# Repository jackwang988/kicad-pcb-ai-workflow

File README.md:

# KiCad PCB AI 工作流 · R10.0.2 稳定维护版

> **2026-11-21**：Windows / KiCad 10.0.8 的 60 mm 单面 8×8 LED 案例已完成原理图、PCB、原生 ERC/DRC 与 Gerber/BOM 工程导出，最终 **0 错误、0 警告、0 未连接**。135 条丝印压焊盘、64 条重叠、80 条字段差异的修复已沉淀为可复用指南。
>
> **稳定范围**：软件回归与公开单板 native 验证，不是全部 16 节点/板型/平台或硬件性能认证。实例字段编辑依赖单独构建、登记和验证的开源 MCP companion；**官方 Konnect 0.14.1 不能直接执行该编辑**。正式 freeze/工程签字、板厂 CAM/EQ、CPL、实物通电/热测试仍独立或未覆盖。

[最新 Release/校验和](https://github.com/jackwang988/kicad-pcb-ai-workflow/releases/latest) · [R10.0.2 说明](R10_0_2_RELEASE_NOTES.md) · [完整实测经验](docs/r10/07-led-e2e-and-silkscreen.md) · [源板与证据](development/fixtures/led-8x8-12v) · [开源 MCP companion](development/konnect-field-extension)

最小 Skill ZIP 只含通用技能；样板、测试与 AGPL 补丁源码在独立 validation ZIP/仓库中。不携带编译器、商业后端或个人配置。正式产物以通过 CI 后生成的 ZIP/SHA/提交 provenance 为准。

## 早期 R10 验收记录（保留历史）

> **R10.0.0 软件稳定版发布目标（2026-11-18）**：基于已合并的 [PR #6](https://github.com/jackwang988/kicad-pcb-ai-workflow/pull/6)、[PR #7](https://github.com/jackwang988/kicad-pcb-ai-workflow/pull/7) 及 [GND 保护修复 PR #9](https://github.com/jackwang988/kicad-pcb-ai-workflow/pull/9)。原生 KiCad→Freerouting→SES→KiCad 保护测试已通过；正式 ZIP/标签须由 [稳定版 CI](.github/workflows/release-r10-stable.yml) 在 main 重新通过软件与原生测试后创建。**软件稳定≠任意PCB自动通过 G4 或授权投产。**
>
> **已验证范围**：KiCad 10.0.8 / Freerouting 2.5.0 隔离样板中，8条普通网络走线回导成功、GND新增走线为0（[原生测试](https://github.com/jackwang988/kicad-pcb-ai-workflow/actions/runs/44295612537)）；该样板仍有原生DRC 9项违规与2项未连接，**不能称为G4通过**。更复杂的多层/高速/电源产品必须独立验收。

> **R10 维护者正式验收补充（2026-11-18）**：维护者确认 GND 优先铺铜规则的 Skill 验证通过，[PR #10](https://github.com/jackwang988/kicad-pcb-ai-workflow/pull/10) 已合并至 `main`（提交 [`86b363f4408a`](https://github.com/jackwang988/kicad-pcb-ai-workflow/commit/86b363f4408af9b5cbd9a9eb7a972f9f65739555)）。现行流程强制**先第一次GND填铜→地铜连通与孤岛检查→按需添加批准的缝合地孔→再次填铜保存→全板DRC→G4**。维护者验收单独登记；[PR #12](https://github.com/jackwang988/kicad-pcb-ai-workflow/pull/12) 又修复了 KiCad 10 名称式网络及板文件格式规范化，[原生铺铜集成 CI #44331681459](https://github.com/jackwang988/kicad-pcb-ai-workflow/actions/runs/44331681459) **已通过**（首铺 F.Cu/B.Cu → 审核地孔 → 再次铺铜 → 原生 DRC）；但该合成样板 DRC 仍有 **13 项违规、3 项未连接**，因此 **并非 G4/制造放行**。详见 [R10 验收矩阵](docs/r10/05-release-readiness.md)。已有的 `R10.0.0` 标签是本次 PR #10 之前的历史快照，不能据此认定旧版ZIP包括新流程。

[核对 R10 正式版 Release 与 ZIP/SHA](https://github.com/jackwang988/kicad-pcb-ai-workflow/releases) · [R10.0.0 说明](R10_STABLE_RELEASE_NOTES.md) · [当前源码](https://github.com/jackwang988/kicad-pcb-ai-workflow/tree/main/kicad-pcb-ai-workflow) · [16节点及七阶段完整流程图](docs/r10/06-current-skill-full-flow.md) · [布线工程契约](kicad-pcb-ai-workflow/references/freerouting-seven-stage.md) · [验收矩阵](docs/r10/05-release-readiness.md) · [R9.4历史包](dist/kicad-pcb-ai-workflow-R9.4.zip)

## 一、R10 核心架构

```mermaid
flowchart TD
  U["用户需求 / 已有 KiCad 项目"] --> W["唯一工作工程 CURRENT_PROJECT.json"]
  W --> S["原厂资料缓存 / 芯片知识卡 / 精确网络拓扑"]
  S --> R["系统架构与原理图预布局 → G1 ERC → G2 封装"]
  R --> D["真实叠层 / NetClass / 制造规则生效与回读"]
  D --> P["Konnect 布局 / 保存与位置回读 → G3"]
  P --> C["关键网络由已验收 KiCad/Konnect 优先布线"]
  C --> F["Freerouting 2.5.0 普通网络 DSN → SES 候选"]
  F --> I["独立 KiCad 候选回导、保存重载、差异审核"]
  I --> O["有界修复 / GND 铺铜 / 原生完整 DRC"]
  O --> G["G4 逐层 PCB 审核 / 工程师确认"]
  G --> N["DFX/NPI → 冻结制造候选 Gerber/BOM/CPL"]
  N --> X["外部 CAM/EQ/工厂授权与试产（非 AI 自动放行）"]
  G -->|风险或证据未关闭| D
```

- **决策层**：AI结合需求、原厂资料、真实网络拓扑和工程规则生成受约束的操作计划；不能编造 datasheet、阻抗、层叠或通过结果。
- **执行层**：Konnect MCP是活动EDA工程的唯一受控写入者；动态发现实际能力，每次授权、写入、保存、回读和异常复核。Python负责只读解析、计算、规则/几何审计与证据绑定；KiCad原生CLI负责独立 ERC/DRC 与制造导出核验。
- **证据层**：器件卡片按制造商＋精确MPN＋封装缓存并复用于 G1/G2/G3/G4；单一权威 `01_WORKING` 工程、只读历史、不可覆盖里程碑、摘要阅读与完整本地审计证据同时保留。
- **门禁层**：任何未知网络、未生效规则、缺失工具、超出权限的改动、过期哈希或未关闭阻断问题均 `BLOCKED`；不能通过降低规则或删除对象制造通过状态。

## 二、16 节点工程全流程

| 节点 | 操作与真实产物 | 门禁 |
|---|---|---|
| 01–04 | 环境/工作区保护 → 量化需求与架构 → 原厂器件知识卡 → 0Ω/DNP/备用方案决策 | 输入来源与工程身份可追溯 |
| 05–07 | **先网络拓扑、预留布线通道及引脚空间，再摆放原理图器件** → 保存原生网络表/ERC → 符号封装脚号比对 | **G1 原理图，G2 封装** |
| 08 | 与板厂确认层叠、铜厚、线宽/线距、过孔、板边、差分/电源约束；在KiCad真实设置并回读 | 规则未生效不能布局/布线 |
| 09 | 连接器/安装孔锚定、模块布局、去耦与关键回路优化，Konnect保存及坐标回读 | **G3 仅布局专项审核**，允许飞线，**不做未布线全板DRC** |
| 10 | **关键网络优先 → Freerouting 普通网络 → SES回导 → 有界修复 → GND铺铜 → 原生DRC** | 七阶段布线契约及实际保存板审计 |
| 11 | 布线、过孔、参考地、回流路径、全部铜层、真实原生 DRC 和工程师确认 | **G4 最终PCB评审** |
| 12–13 | DFX/NPI → 独立冻结制造候选 → Gerber/Excellon/BOM/CPL/图纸及哈希 | `EXPORTED_NOT_RELEASED` |
| 14–16 | 工厂CAM/EQ与放行 → EVT/DVT/PVT → ECO归档 | **外部人工/实体流程**，不是AI自动执行或自动批准 |

详细输入/输出/失败回退：[最新全流程说明](kicad-pcb-ai-workflow/references/latest-complete-workflow.md)；[完整架构与实际运行流程图](docs/r10/06-current-skill-full-flow.md)。

## 三、PCB 七阶段布线执行标准（R10）

1. **完整网络清单**：依据保存的 KiCad PCB 和原生 XML Netlist 确定全部网络、`(Ref, Pin)` 端点、P0–P4 分类、电流、关键性、GND/NC，并检查真实 NetClass 归属。
2. **制造与设计规则先行**：取得板厂批准的层叠、铜厚、最小线宽/线距/过孔/板边，配置真实 NetClass、层限制、电源宽度、差分/等长及禁布区并重新读取验证。电源主干以实际电流/温升/压降计算和既定基准线宽为依据，额外保留**至少 0.254 mm 线宽余量**（不是统一固定宽度）；细脚仅允许经批准、有长度/区域上限的局部颈缩。
3. **关键网络优先并保护**：P0–P2等高优先级（高速/RF/差分/电源/Kelvin/时钟/开关回路）由已验收的 KiCad/Konnect 专项方式布线；保存、回读实际铜对象，保护原走线与锁定对象。
4. **Freerouting 2.5.0 批量普通网络**：保存 PCB 后导出 DSN，绑定 DSN/JAR 及获批准的 `.rules` SHA-256，使用 `-inc` 按**NetClass**排除 GND 与所有受保护网络类别；仅路由允许的普通 P3 网络，限制重试/时间/过孔，产生独立 `.ses` 候选。`-inc` 不是按网络名称排除；NetClass 必须确实覆盖全部网络。
5. **SES 导入与真实几何审核**：仅在隔离 KiCad 候选中经认可工具回导，保存/重载，对比网络、封装位置、原有关键铜与对象UUID，审核普通网络线宽、层、过孔、H/V/45°走线及完整性。**生成 SES 不等于成功布线。**
6. **有界修复**：仅处理明确的未连接项或获准的拆线白名单；执行前确认范围/限额，改动后重复真实回读；失败或工具缺失则阻断并交由工程师处理，不默认放宽工艺/电气规则。
7. **GND 首次铺铜 → 检查地铜连通 → 按需补地孔 → 再次铺铜 → 全板 DRC/G4**：GND不参与普通走线。先在批准的GND铜层真实覆铜并保存，审核孤岛、焊盘、回流路径和跨层铜区；仅在必要、合法且经批准的位置放置GND缝合过孔（并非见空白就打孔），**之后重新填铜、保存重载**。四份PCB快照通过只读 `pcb.ground_plane_audit`，才能执行 `kicad-cli pcb drc --refill-zones --save-board` 全板DRC与未连接检查。DRC不为零继续修复并再次覆铜；G4工程师签核独立。**铺铜前GND飞线不是最终DRC故障。**

[GND 铺铜、跨层地孔与 DRC 前置门禁规范](kicad-pcb-ai-workflow/references/gnd-before-drc.md)。GND 有多层填充不自动证明各层互连，最终须检查实际接触和原生网络连通性。

**注意**：Freerouting 2.5.0 不保证自动满足任意 KiCad 自定义 DRC、受控阻抗/等长/回流/局部颈缩，也不能仅凭 DSN/SES 证明最终角度45°；由导入后的实际铜和原生检查判定。审核脚本**只读**，不会自行执行 SES 导入、GND铺铜或原生DRC。

[七阶段详细参数与命令](kicad-pcb-ai-workflow/references/freerouting-seven-stage.md) · [主次布线与 NetClass 技术边界](kicad-pcb-ai-workflow/references/freerouting-primary-routing.md) · [设计约束](kicad-pcb-ai-workflow/references/constraint-routing.md)

## 四、部署与示例命令

**实际 Skill 位于仓库内的 [`kicad-pcb-ai-workflow/` 子目录](kicad-pcb-ai-workflow/)**，只安装这一层（包含 `SKILL.md`、`scripts/`、`references/`、`assets/`）。仓库根目录不是Skill安装目录。

- **使用R10当前源码**：`git clone https://github.com/jackwang988/kicad-pcb-ai-workflow.git`，再将仓库内部的 `kicad-pcb-ai-workflow/` 目录安装到 Agent Skills 目录。更新时以新目录完整替换、核对文件和原工程备份，勿与旧脚本混装。
- **已有正式包**：[R9.4稳定包](dist/kicad-pcb-ai-workflow-R9.4.zip)和 [R10.0.0-rc.1历史预发布包](dist/kicad-pcb-ai-workflow-R10.0.0-rc.1.zip)不包含本次全部合并改动；**不要当作最新版七阶段布线包**。
- **环境依赖**：匹配版本的 KiCad CLI/原生工程、可用的 Konnect MCP，普通网络自动布线还需要经SHA验证的 Freerouting **2.5.0 JAR** 和 Java，以及明确批准的厂规。Konnect/Freerouting为独立外部工具，不随Skill自动安装。`jsonschema>=4.18,<5` 见 [requirements.txt](requirements.txt)。
- **版本**：KiCad 10.0.7为历史推荐基线；KiCad 10.0.8曾完成独立原生工具链烟测。其它10.x必须实际验证能力；KiCad 9尚未开放未经验证的原生生产能力；KiCad 11+的CLI-only候选不等于PCB写入适配。

在Skill目录中以本机正确Python解释器运行，先预览、核对目标工程，再按需 `--apply`：

```bash
python scripts/workflow.py run /path/project --task environment.doctor
python scripts/workflow.py workspace /path/project --action status
python scripts/workflow.py status /path/project --bundle control-r1 --format compact
python scripts/workflow.py modules --intent pcb
python scripts/routing_seven_stage.py plan /path/project --config route-plan-config.json
# 仅在取得真实DSN/NetClass及厂规审核后运行候选
python scripts/freerouting_adapter.py --dsn route/board.dsn \
  --expected-dsn-sha256 ACTUAL_DSN_SHA \
  --netclass-map route/netclass-map.json \
  --expected-netclass-map-sha256 APPROVED_NATIVE_MAP_SHA \
  --jar approved/freerouting-2.5.0.jar \
  --expected-jar-sha256 APPROVED_JAR_SHA \
  --exclude-netclasses GND,DIFF_CRITICAL,RF_CRITICAL,POWER_CRITICAL \
  --output-dir NEW_CANDIDATE --passes 20
# 真实SES须在独立KiCad/Konnect工程中导入、保存、重载，再审计：
python scripts/routing_seven_stage.py audit-import /path/project --config route-import-config.json
# Konnect 在保存的 PCB 上先实际铺GND → 如需则添加已批准地孔 → 再次铺铜和保存重载。
python scripts/routing_seven_stage.py audit-ground /path/project --config ground-config.json --output reports/ground-pre-drc.json
# 只有审核通过，才能对完成铺铜的候选板运行全板 DRC：
kicad-cli pcb drc --refill-zones --save-board --format json --output reports/final-drc.json /path/project/checkpoints/final-refilled.kicad_pcb
# 再次保存回读，最后用 ground gate、post-DRC board 与 DRC report 的 SHA 审核：
python scripts/routing_seven_stage.py audit-final /path/project --config route-final-config.json
```

以上 Freerouting 命令默认仅生成预览，参数值和类名是示例，实际批准后再执行 `--apply`；如有 `.rules` 还必须显式给出其路径和SHA。参考 [环境配置](kicad-pcb-ai-workflow/references/environment-onboarding.md)、[工作区保护](kicad-pcb-ai-workflow/references/workspace-and-token-policy.md) 与 [模块化执行说明](kicad-pcb-ai-workflow/references/module-pcb.md)。

## 五、软件验收、原生验收与制造边界

| 层级 | 截至 2026-11-18 的状态 |
|---|---|
| PR #6 软件 CI | [已通过](https://github.com/jackwang988/kicad-pcb-ai-workflow/actions/runs/44278478257) |
| PR #7 软件 CI | [已通过](https://github.com/jackwang988/kicad-pcb-ai-workflow/actions/runs/44287952061) |
| KiCad 10.0.8 基础原生工具链 | [历史隔离工程烟测通过](https://github.com/jackwang988/kicad-pcb-ai-workflow/actions/runs/44015065144)，不等于新路由全链通过 |
| Windows/Konnect 本机 | **维护者报告已验收通过**；当前仓库没有相应的新现场日志/录屏可供独立复核 |
| KiCad→Freerouting 2.5.0→SES→KiCad 原生往返 | **PASS_NOT_G4**：[#44295612537](https://github.com/jackwang988/kicad-pcb-ai-workflow/actions/runs/44295612537)。GND在真实DSN中归属GND类；禁用v2.5.0 Fanout/Optimizer后，KiCad回导保存得到8条普通网线、0条新增GND铜线；旧版路由夹具在未铺地铜时出现过9项违规与2项未连；**不属于G4判定**。路由互通夹具已停止铺铜前全板DRC |
| PR #10 维护者 Skill 验收和源码合并 | **维护者已确认 PASS；[PR #10](https://github.com/jackwang988/kicad-pcb-ai-workflow/pull/10) 已合入 main**，含首次GND填充→批准地孔→再次填充→最终DRC门禁 |
| PR #10 软件 CI | [通过 #44321219956](https://github.com/jackwang988/kicad-pcb-ai-workflow/actions/runs/44321219956) |
| PR #12 原生铺铜修复及验收 | [**PASS_NOT_G4 · #44331681459**](https://github.com/jackwang988/kicad-pcb-ai-workflow/actions/runs/44331681459)：KiCad 10 双层 GND 首次铺铜、受审 GND 地孔、再次铺铜、保存回读、独立 DRC 实际执行；合成板仍有13项 DRC 违规/3项未连（非量产放行） |
| 不同层数/高速与电源混合项目、CAM/试产 | 未作为自动化通用能力认证；每个真实产品需独立验收 |

**修复记录（[PR #9](https://github.com/jackwang988/kicad-pcb-ai-workflow/pull/9) / [Issue #8](https://github.com/jackwang988/kicad-pcb-ai-workflow/issues/8)）**：仅有 NetClass 名称声明不够；必须校验网络实际 DSN 类成员与独立原生 `net_to_class` 全量映射及SHA-256。Freerouting 2.5.0 的 Fanout/Optimizer 在先前测试中绕开了GND保护，因此 R10普通网批量布线默认关闭这两阶段；回导后的受保护铜线差异审核继续强制执行。支持范围外保持 BLOCKED。

**软件发布不等于 PCB 可投产授权。** 源码测试、保存板上的G4 DRC、工程师的电气/热/高速审核以及板厂CAM/EQ/样机测试是独立步骤。Gerber、钻孔、BOM、CPL 导出成功仍标记 `EXPORTED_NOT_RELEASED`。

## 六、更多说明

[R10当前系统全流程与架构图](docs/r10/06-current-skill-full-flow.md) · [R10文档导航](docs/r10/README.md) · [原厂推荐电路与器件卡](kicad-pcb-ai-workflow/references/device-knowledge.md) · [原理图预布局门禁](kicad-pcb-ai-workflow/references/schematic-preplacement.md) · [G3布局规则](kicad-pcb-ai-workflow/references/placement-quality.md) · [DFX/NPI](kicad-pcb-ai-workflow/references/dfx-npi.md) · [能力与限制](kicad-pcb-ai-workflow/references/capabilities.md) · [MIT](LICENSE)

作者：[Jack](https://github.com/jackwang988) · 许可证：MIT。

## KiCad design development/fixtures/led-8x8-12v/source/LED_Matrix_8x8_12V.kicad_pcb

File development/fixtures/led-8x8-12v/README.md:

# Saved single-copper LED regression case

Source board SHA-256: `ff3a1ec530da8b8f27dfba17465142b448248b9a575763b118718e2d97a0c7ea`.
The nine source files are byte-identical to the final MCP-saved engineering export snapshot. Per-user `.kicad_prl`, logs, IPC configuration, executable files and absolute workstation paths are excluded. Exact source hashes and the local observation's **unverified** areas are in `evidence/observed-validation.json`.

60×60 mm, 8×8 red 2835 LEDs, 7.5 mm pitch, sixteen 4-LED + 1 kohm branches, 12 V DC, F.Cu only, no holes/vias. LED: Wurth Elektronik 150283RS73103, pin 1 anode / pin 2 cathode. Resistor: 1 kohm, 1%, 1206, 0.25 W; supplier/MPN unspecified. J1–J4 are PCB solder-pad pairs. Design material/thickness/copper are assumptions, not factory acceptance. See `design-basis.md`; this is a low-current workflow test, not an electrically measured product.

```sh
python -m pip install -r development/requirements-led-validation.txt
python development/native_led_8x8_e2e.py --kicad-cli /path/to/kicad-cli --output /new/native-led-check
```

Requires exact KiCad 10.0.8 plus its standard resistor footprint library, `power` symbol library and project custom libraries. On a new installation initialize **both** standard `fp-lib-table` and `sym-lib-table` through the normal installer/configuration. Installing library packages alone does not register them: the first clean Linux CI run correctly stopped on 44 missing-`power` ERC warnings. CI now initializes both tables in its disposable runner; the verifier never edits host library configuration or suppresses these warnings. The script exports/checks a new copy, compares all pads/tracks and net partitions, and requires zero native ERC/DRC warnings. It does not write the input, replay design creation, install/register MCP or satisfy the formal freeze/candidate gate.

`evidence/native-DRC.json` / `native-ERC.json` retain the observed zero-warning results. The metadata observation is a maintainer's local record; it is not an independent second-machine test. CI regenerates native reports rather than trusting those JSON counts. The final Gerber PNG is published under `docs/r10/figures` for the case account.

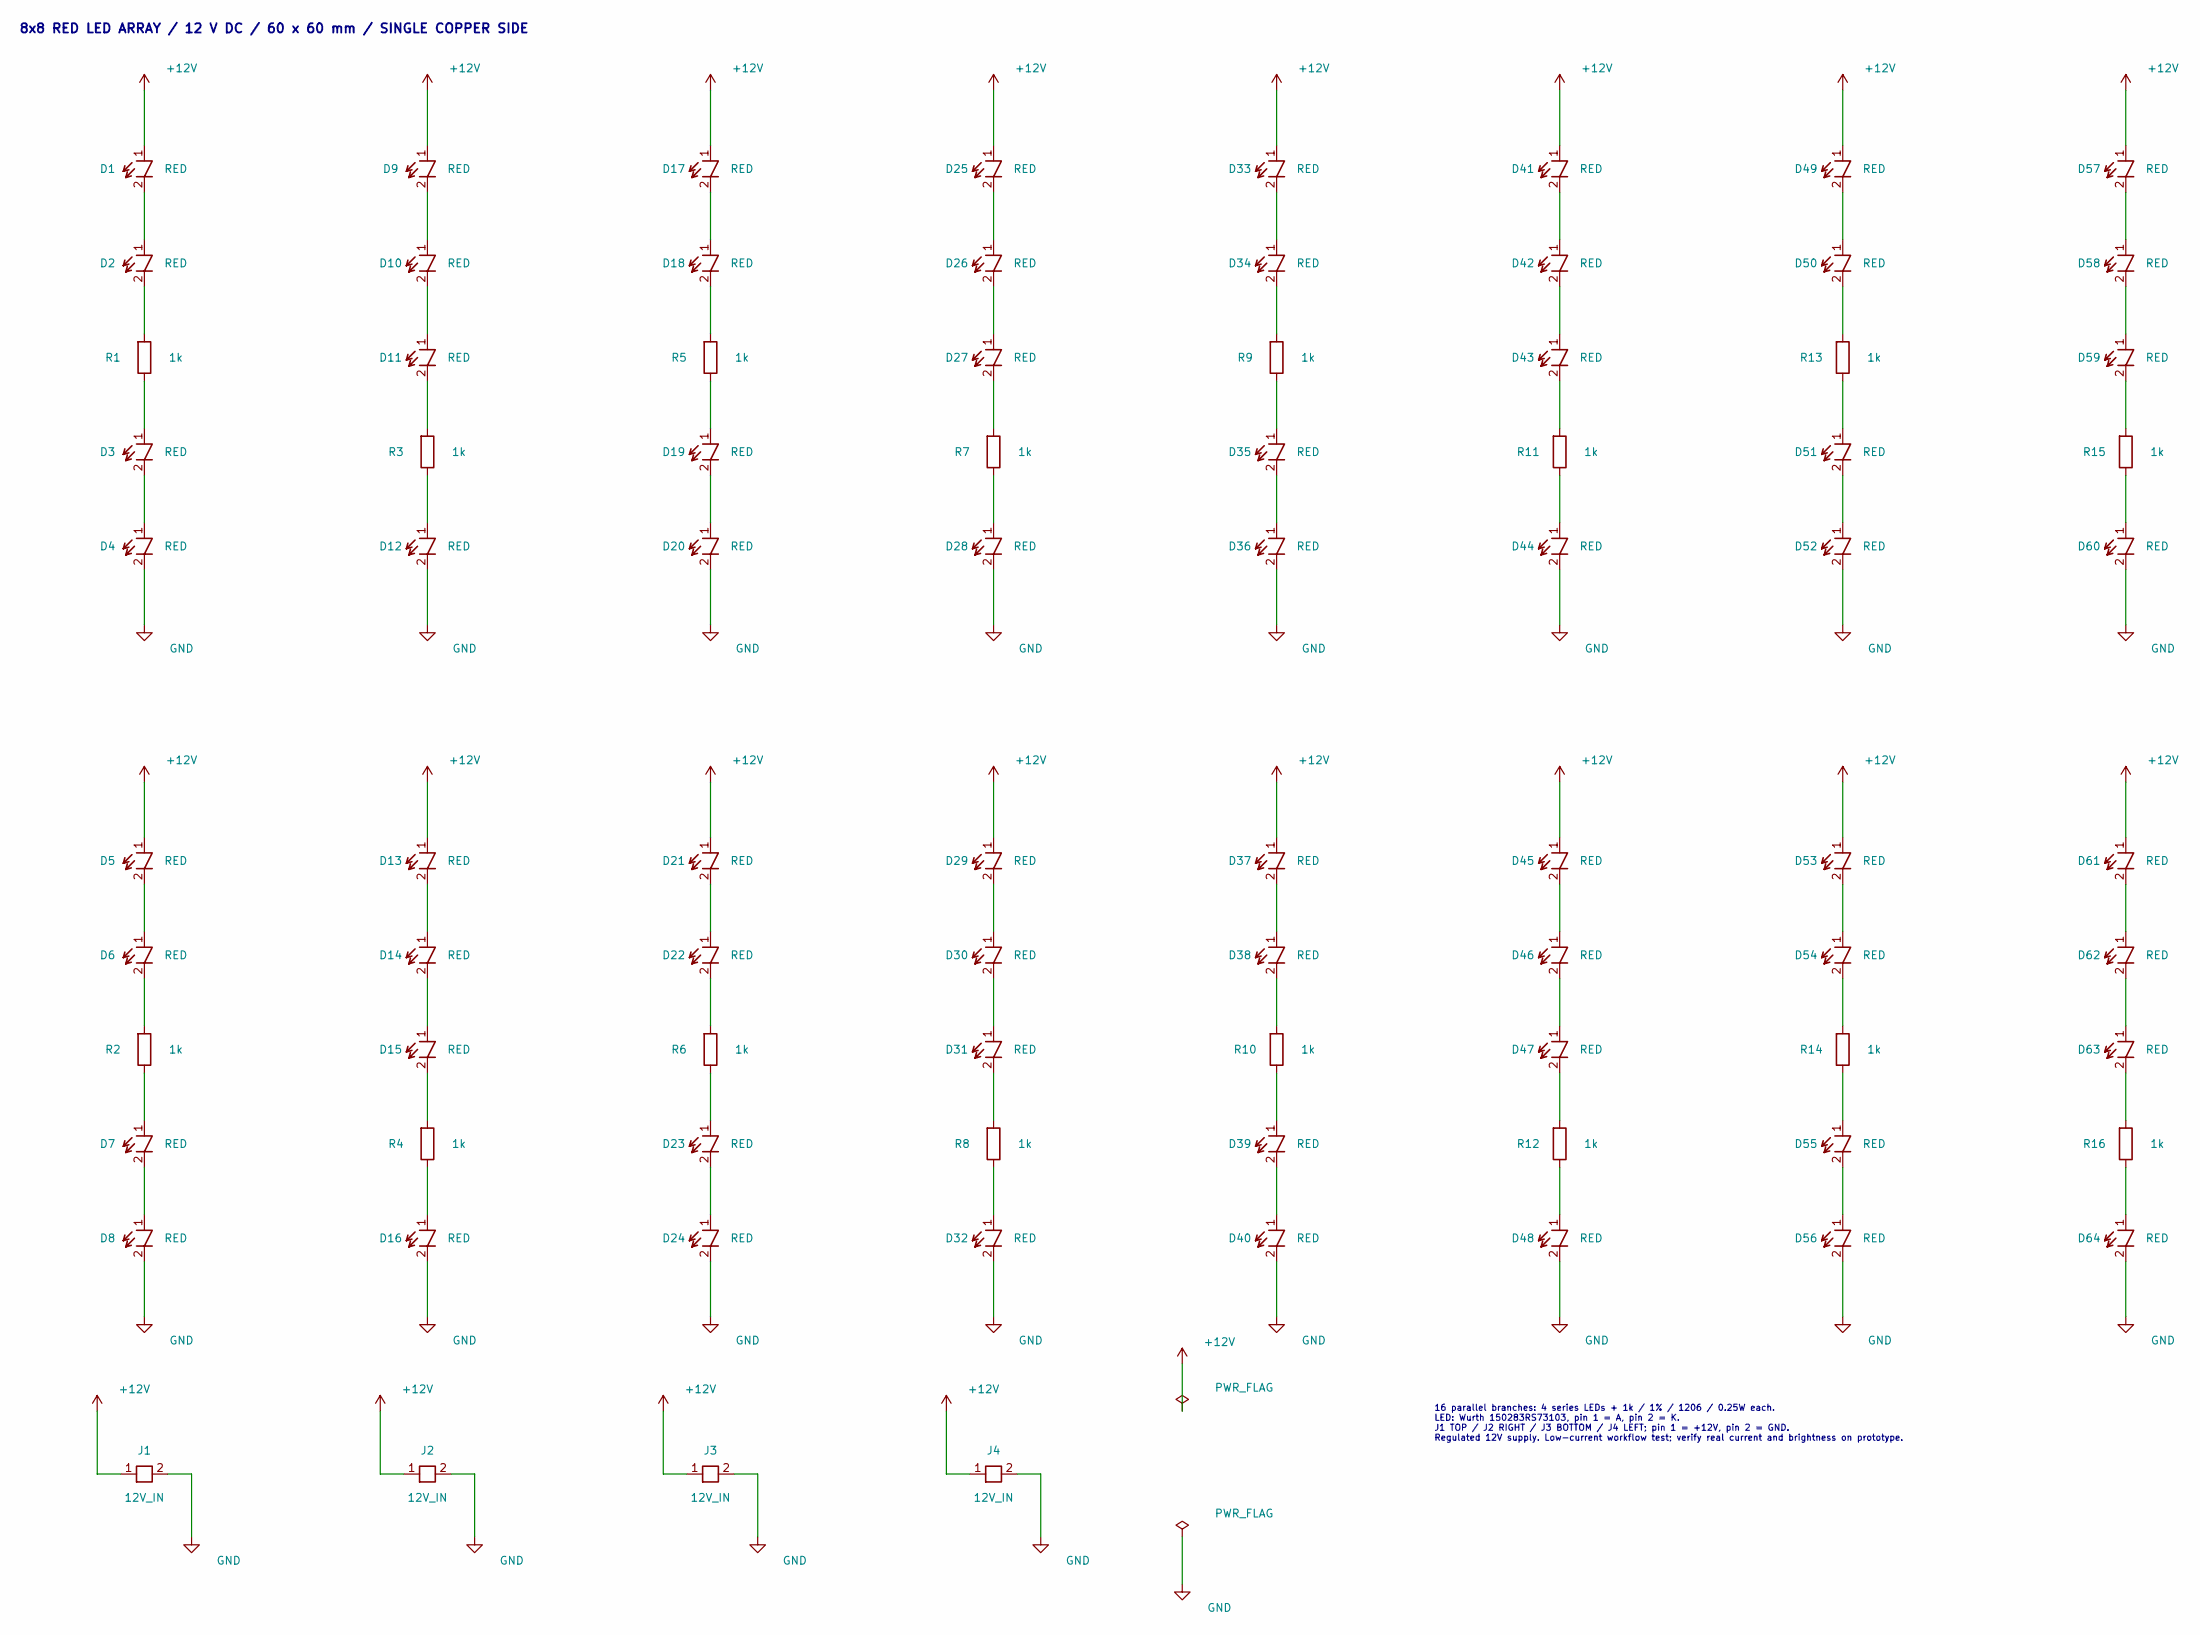
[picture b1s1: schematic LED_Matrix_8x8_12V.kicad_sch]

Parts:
D1, D2, D3, D4, D5, D6, D7, D8, D9, D10, D11, D12, D13, D14, D15, D16, D17, D18, D19, D20, D21, D22, D23, D24, D25, D26, D27, D28, D29, D30, D31, D32, D33, D34, D35, D36, D37, D38, D39, D40, D41, D42, D43, D44, D45, D46, D47, D48, D49, D50, D51, D52, D53, D54, D55, D56, D57, D58, D59, D60, D61, D62, D63, D64: RED; WE_150283RS73103; MPN 150283RS73103
J1, J2, J3, J4: 12V_IN; Edge_Power_Pair
R1, R2, R3, R4, R5, R6, R7, R8, R9, R10, R11, R12, R13, R14, R15, R16: 1k; R_1206_3216Metric

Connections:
+12V: D1.1 (A), D5.1 (A), D9.1 (A), D13.1 (A), D17.1 (A), D21.1 (A), D25.1 (A), D29.1 (A), D33.1 (A), D37.1 (A), D41.1 (A), D45.1 (A), D49.1 (A), D53.1 (A), D57.1 (A), D61.1 (A), J1.1 (+12V), J2.1 (+12V), J3.1 (+12V), J4.1 (+12V)
GND: D4.2 (K), D8.2 (K), D12.2 (K), D16.2 (K), D20.2 (K), D24.2 (K), D28.2 (K), D32.2 (K), D36.2 (K), D40.2 (K), D44.2 (K), D48.2 (K), D52.2 (K), D56.2 (K), D60.2 (K), D64.2 (K), J1.2 (GND), J2.2 (GND), J3.2 (GND), J4.2 (GND)
unnamed: D1.2 (K), D2.1 (A)
unnamed: D2.2 (K), R1.1
unnamed: D3.1 (A), R1.2
unnamed: D3.2 (K), D4.1 (A)
unnamed: D5.2 (K), D6.1 (A)
unnamed: D6.2 (K), R2.1
unnamed: D7.1 (A), R2.2
unnamed: D7.2 (K), D8.1 (A)
unnamed: D9.2 (K), D10.1 (A)
unnamed: D10.2 (K), D11.1 (A)
unnamed: D11.2 (K), R3.1
unnamed: D12.1 (A), R3.2
unnamed: D13.2 (K), D14.1 (A)
unnamed: D14.2 (K), D15.1 (A)
unnamed: D15.2 (K), R4.1
unnamed: D16.1 (A), R4.2
unnamed: D17.2 (K), D18.1 (A)
unnamed: D18.2 (K), R5.1
unnamed: D19.1 (A), R5.2
unnamed: D19.2 (K), D20.1 (A)
unnamed: D21.2 (K), D22.1 (A)
unnamed: D22.2 (K), R6.1
unnamed: D23.1 (A), R6.2
unnamed: D23.2 (K), D24.1 (A)
unnamed: D25.2 (K), D26.1 (A)
unnamed: D26.2 (K), D27.1 (A)
unnamed: D27.2 (K), R7.1
unnamed: D28.1 (A), R7.2
unnamed: D29.2 (K), D30.1 (A)
unnamed: D30.2 (K), D31.1 (A)
unnamed: D31.2 (K), R8.1
unnamed: D32.1 (A), R8.2
unnamed: D33.2 (K), D34.1 (A)
unnamed: D34.2 (K), R9.1
unnamed: D35.1 (A), R9.2
unnamed: D35.2 (K), D36.1 (A)
unnamed: D37.2 (K), D38.1 (A)
unnamed: D38.2 (K), R10.1
unnamed: D39.1 (A), R10.2
unnamed: D39.2 (K), D40.1 (A)
unnamed: D41.2 (K), D42.1 (A)
unnamed: D42.2 (K), D43.1 (A)
unnamed: D43.2 (K), R11.1
unnamed: D44.1 (A), R11.2
unnamed: D45.2 (K), D46.1 (A)
unnamed: D46.2 (K), D47.1 (A)
unnamed: D47.2 (K), R12.1
unnamed: D48.1 (A), R12.2
unnamed: D49.2 (K), D50.1 (A)
unnamed: D50.2 (K), R13.1
unnamed: D51.1 (A), R13.2
unnamed: D51.2 (K), D52.1 (A)
unnamed: D53.2 (K), D54.1 (A)
unnamed: D54.2 (K), R14.1
unnamed: D55.1 (A), R14.2
unnamed: D55.2 (K), D56.1 (A)
unnamed: D57.2 (K), D58.1 (A)
unnamed: D58.2 (K), D59.1 (A)
unnamed: D59.2 (K), R15.1
unnamed: D60.1 (A), R15.2
unnamed: D61.2 (K), D62.1 (A)
unnamed: D62.2 (K), D63.1 (A)
unnamed: D63.2 (K), R16.1
unnamed: D64.1 (A), R16.2

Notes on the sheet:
8x8 RED LED ARRAY / 12 V DC / 60 x 60 mm / SINGLE COPPER SIDE
16 parallel branches: 4 series LEDs + 1k / 1% / 1206 / 0.25W each. LED: Wurth 150283RS73103, pin 1 = A, pin 2 = K. J1 TOP / J2 RIGHT / J3 BOTTOM / J4 LEFT; pin 1 = +12V, pin 2 = GND. Regulated 12V supply. Low-current workflow test; verify real current and brightness on prototype.

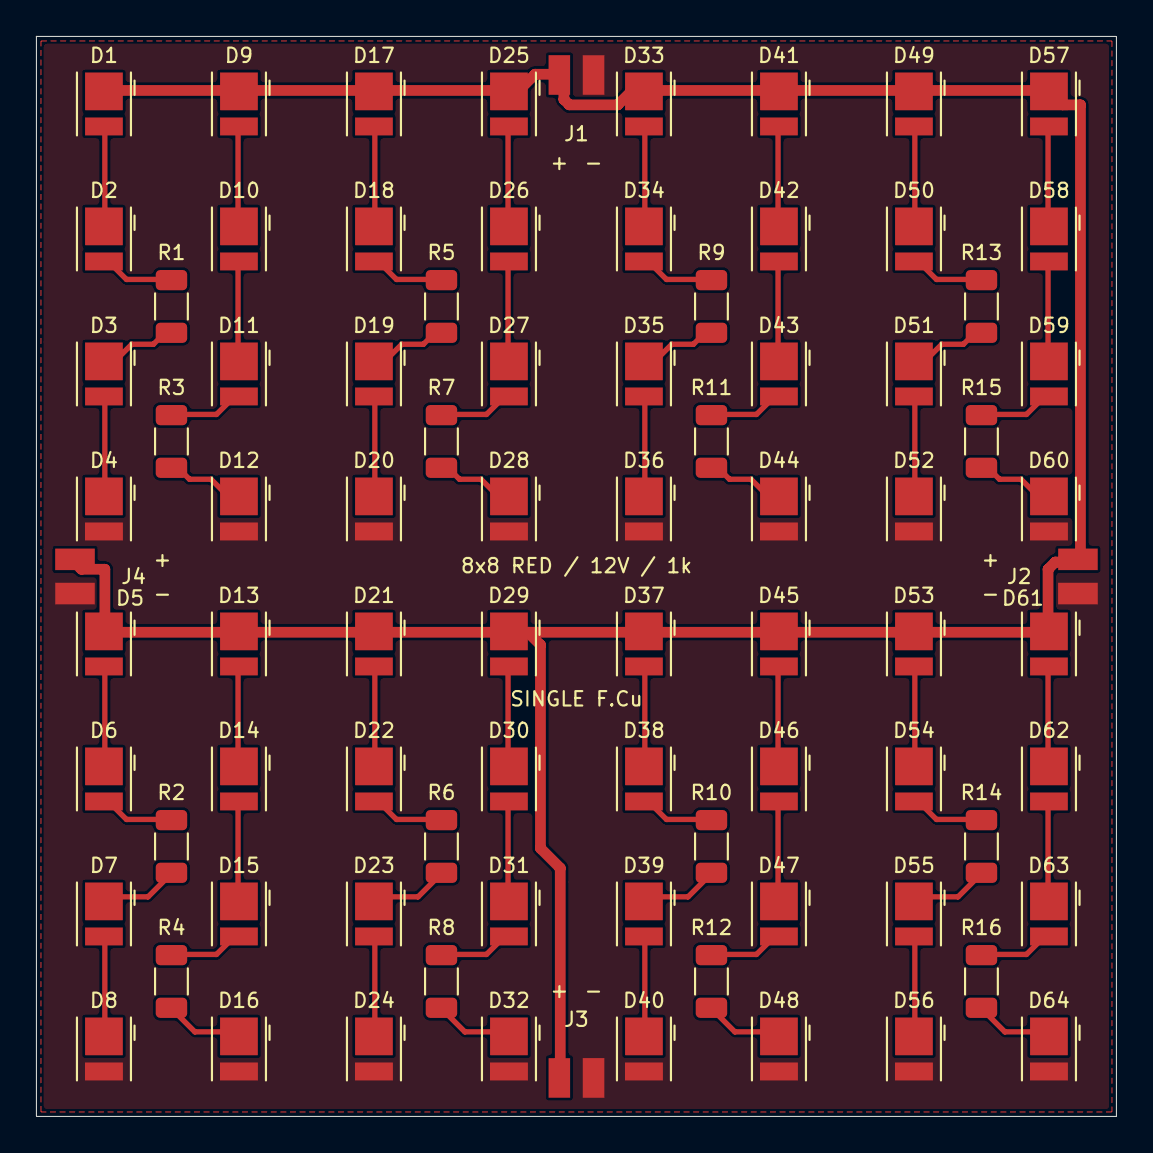
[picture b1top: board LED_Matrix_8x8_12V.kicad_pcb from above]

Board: 2 copper layers, 60.0 x 60.0 mm, 84 parts (0 on the bottom side), 66 nets.

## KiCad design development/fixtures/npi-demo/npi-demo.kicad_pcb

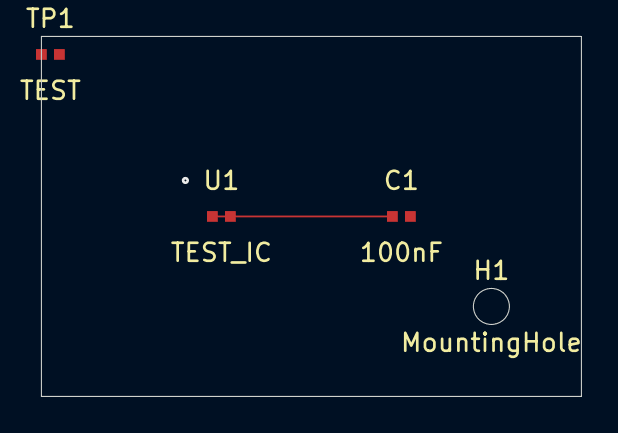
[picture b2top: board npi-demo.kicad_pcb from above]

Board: 2 copper layers, 30.0 x 20.0 mm, 4 parts (0 on the bottom side), 2 nets.

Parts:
C1: 100nF; Fixture
H1: MountingHole; Fixture
TP1: TEST; Fixture
U1: TEST_IC; Fixture

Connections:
+3V3: C1.1, TP1.1, U1.1
GND: C1.2, TP1.2, U1.2

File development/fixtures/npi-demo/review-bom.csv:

Reference,MPN,Manufacturer,Footprint,Value
U1,DEMO-IC,DEMO,NPI:Fixture,TEST_IC
C1,DEMO-CAP,,NPI:Fixture,100nF
TP1,DEMO-TP,DEMO,NPI:Fixture,TEST
H1,DEMO-HOLE,DEMO,NPI:Fixture,MountingHole

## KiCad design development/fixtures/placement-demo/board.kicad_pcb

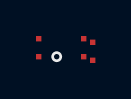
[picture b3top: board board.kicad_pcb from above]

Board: 2 copper layers, 3 parts (0 on the bottom side), 2 nets, no tracks yet.

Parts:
C1: TEST
R1: TEST
U1: TEST

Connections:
GND: C1.2, R1.2, U1.2
VDD: C1.1, U1.1
